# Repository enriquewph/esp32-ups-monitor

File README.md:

# Migrated
Pleas check [https://github.com/enriquewph/esp-map](https://github.com/enriquewph/esp-map)

# ups-central-fw
Firmware para ESP32 en UPS Central

# Necessary secrets.h file:
Place it here **lib/secrets/secrets.h**
It should have the next format
```c
#ifndef SECRETS_H
#define SECRETS_H

#define WIFI_SSID "MyWiFiSSID"
#define WIFI_PW "some_secret_password"

#endif
```

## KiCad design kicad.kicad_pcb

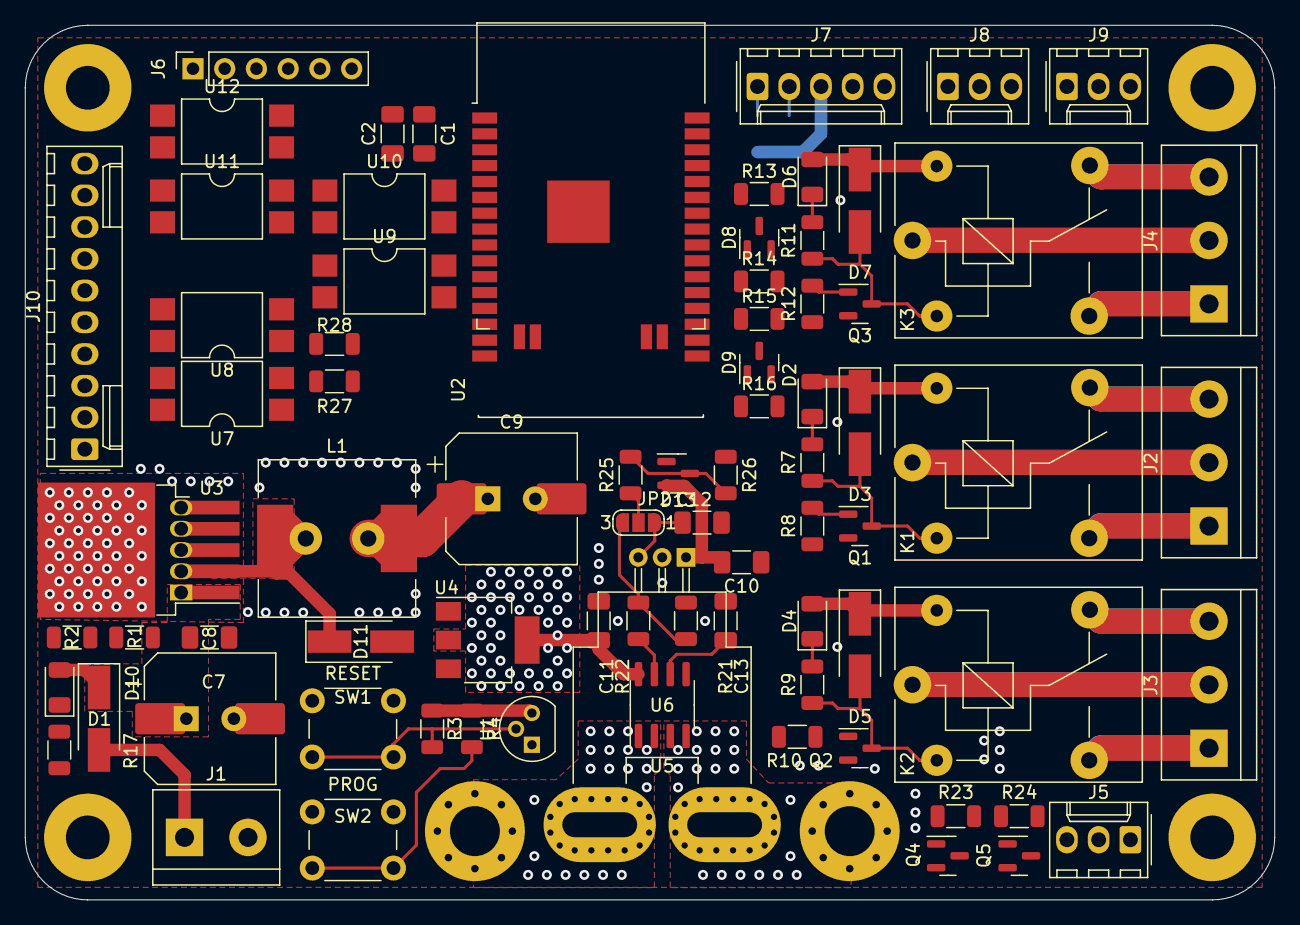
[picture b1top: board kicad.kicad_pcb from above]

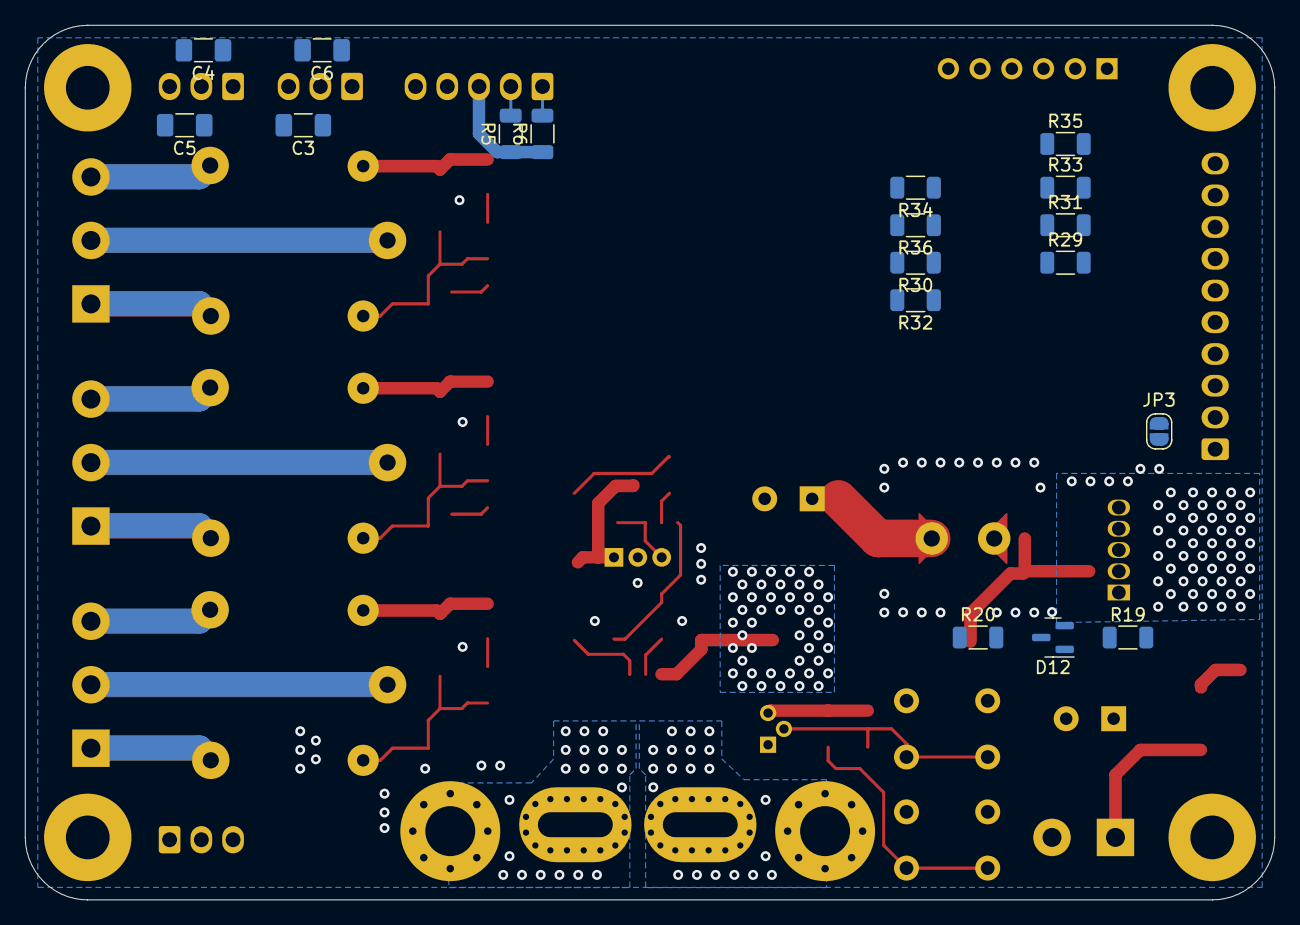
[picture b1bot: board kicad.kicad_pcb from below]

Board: 2 copper layers, 100.0 x 70.0 mm, 98 parts (18 on the bottom side), 77 nets.

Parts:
C1, C3, C4, C5, C6, C8, C10, C11, C12: 100nF; C_1206_3216Metric_Pad1.33x1.80mm_HandSolder
C2: 1uF; C_1206_3216Metric_Pad1.33x1.80mm_HandSolder
C7, C9: 470uF; CAP_10x10_SMD_THT
C13: 1nF; C_1206_3216Metric_Pad1.33x1.80mm_HandSolder
D1, D11: SS14; D_SMA_Handsoldering
D2, D4, D6, D10: LED; LED_1206_3216Metric
D3, D5, D7: M7; D_SMA_Handsoldering
D8, D9, D12, D13: BAT54S; SOT-23
H1, H2: MountingHole_Pad; MountingHole_4mm_Pad_Via
J1: Screw_Terminal_01x02; TerminalBlock_bornier-2_P5.08mm
J2, J3, J4: Screw_Terminal_01x03; TerminalBlock_bornier-3_P5.08mm
J5, J8, J9: Conn_01x03; Molex_KK-254_AE-6410-03A_1x03_P2.54mm_Vertical
J6: ICSP; PinSocket_1x06_P2.54mm_Vertical
J7: Conn_01x05; Molex_KK-254_AE-6410-05A_1x05_P2.54mm_Vertical
J10: Conn_01x10; Molex_KK-254_AE-6410-10A_1x10_P2.54mm_Vertical
JP2: SolderJumper_3_Bridged12; SolderJumper-3_P1.3mm_Open_RoundedPad1.0x1.5mm_NumberLabels
JP3: SolderJumper_2_Open; SolderJumper-2_P1.3mm_Open_RoundedPad1.0x1.5mm
K1, K2, K3: RELAY; Relay_SPDT_SANYOU_SRD_Series_Form_C
L1: 68uH; L_12x12mm_H8mm
Q1, Q2, Q3, Q4: BC817; SOT-23
Q5: IRLML2502; SOT-23
R1: 22k; R_1206_3216Metric
R2: 5k6; R_1206_3216Metric
R3, R4, R5, R6, R24, R30, R32, R34, R36: 10k; R_1206_3216Metric
R7, R8, R9, R10, R11, R12, R13, R14, R15, R16, R17, R19, R20, R22, R23, R25, R26, R29, R31, R33, R35: 1k; R_1206_3216Metric
R21: 2k; R_1206_3216Metric
R27, R28: 100; R_1206_3216Metric
SW1, SW2: SW_Push; SW_PUSH_6mm
U1: DS1233A-10; TO-92
U2: ESP32; ESP32-WROOM-WROVER-NC
U3: LM2596S-3.3; TO-263-5_TabPin3
U4: AMS1117-5.0; SOT-223-3_TabPin2
U5: ACS759; Allegro_CB_PFF
U6: ACS712; SOIC-8_3.9x4.9mm_P1.27mm
U7, U8, U9, U10, U11, U12: PC817XI; SMDIP-4_W9.53mm

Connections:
+3V3: C1.1, C2.1, C4.1, C6.1, C9.1, C10.1, D8.2, D9.2, D12.2, D13.2, J6.6, J7.3, J8.1, J9.1, L1.2, R3.1, R4.1, R5.1, R6.1, R30.1, R32.1, R34.1, R36.1, U1.3 (VDD), U2.2 (VDD), U3.4 (FB), U5.1 (VCC), U8.1
+5V: C11.1, J7.4, U4.2 (VO), U6.8 (VCC)
+12V: C7.1, C8.1, D1.1 (K), D2.2 (A), D3.1 (K), D4.2 (A), D5.1 (K), D6.2 (A), D7.1 (K), D10.2 (A), J5.1, JP3.2 (B), K1.5, K2.5, K3.5, R1.1, R24.1, U3.1 (VIN), U4.3 (VI)
+BATT: D1.2 (A), J1.1
/Current Sensor/IP+: H1.1, U5.4 (IP+), U6.1 (IP+), U6.2 (IP+)
/Current Sensor/IP-: H2.1, U5.5 (IP-), U6.3 (IP-), U6.4 (IP-)
/Current Sensor/OUT: JP2.2 (C), R25.2
/Input Protection/IN: R1.2, R2.1, R19.2
/LM35: T1/OUT: C3.1, J8.2, R13.2
/LM35: T2/OUT: C5.1, J9.2, R15.2
/Opto I/O/input-0/A: J10.2, JP3.1 (A), R29.2, R31.2, R33.2, R35.2
/Opto I/O/input-0/K: J10.7, U9.2
/Opto I/O/input-1/K: J10.8, U10.2
/Opto I/O/input-2/K: J10.9, U11.2
/Opto I/O/input-3/K: J10.10, U12.2
/Opto I/O/output-0/C: J10.5, U8.4
/Opto I/O/output-0/E: J10.6, U8.3
/Opto I/O/output-1/C: J10.3, U7.4
/Opto I/O/output-1/E: J10.4, U7.3
/Relay 1/COM: J2.2, K1.1
/Relay 1/NC: J2.3, K1.4
/Relay 1/NO: J2.1, K1.3
/Relay 2/COM: J3.2, K2.1
/Relay 2/NC: J3.3, K2.4
/Relay 2/NO: J3.1, K2.3
/Relay 3/COM: J4.2, K3.1
/Relay 3/NC: J4.3, K3.4
/Relay 3/NO: J4.1, K3.3
/Salida MOSFET/OUT: J5.3, Q5.3 (D)
FAN_1: R23.2, U2.26 (IO4)
GND: C1.2, C2.2, C3.2, C4.2, C5.2, C6.2, C7.2, C8.2, C9.2, C10.2, C11.2, C12.2, C13.2, D8.1, D9.1, D11.2 (A), D12.1, D13.1, J1.2, J6.5, J7.5, J8.3, J9.3, J10.1, Q1.2 (E), Q2.2 (E), Q3.2 (E), Q4.2 (E), Q5.2 (S), R2.2, R17.2, R21.1, SW1.1, SW2.1, U1.1 (GND), U2.1 (GND), U2.15 (GND), U2.38 (GND), U2.39 (GND), U3.3 (GND), U3.5 (~ON/OFF), U4.1 (GND), U5.2 (GND), U6.5 (GND), U7.2, U9.3, U10.3, U11.3, U12.3
GPIO0: J6.4, R4.2, SW2.2, U2.25 (IO0)
IBAT: R26.1, U2.6 (IO34)
IN0: R30.2, U2.10 (IO25), U9.4
IN1: R32.2, U2.11 (IO26), U10.4
IN2: R34.2, U2.8 (IO32), U11.4
IN3: R36.2, U2.9 (IO33), U12.4
unnamed: C12.1, JP2.1 (A), U5.3 (VIOUT)
unnamed: C13.1, U6.6 (FILTER)
unnamed: D2.1 (K), R7.1
unnamed: D3.2 (A), K1.2, Q1.3 (C), R7.2
unnamed: D4.1 (K), R9.1
unnamed: D5.2 (A), K2.2, Q2.3 (C), R9.2
unnamed: D6.1 (K), R11.1
unnamed: D7.2 (A), K3.2, Q3.3 (C), R11.2
unnamed: D8.3, R13.1, R14.2
unnamed: D9.3, R15.1, R16.2
unnamed: D10.1 (K), R17.1
unnamed: D11.1 (K), L1.1, U3.2 (OUT)
unnamed: D12.3, R19.1, R20.2
unnamed: D13.3, R25.1, R26.2
unnamed: JP2.3 (B), R21.2, R22.1
unnamed: Q1.1 (B), R8.1
unnamed: Q2.1 (B), R10.1
unnamed: Q3.1 (B), R12.1
unnamed: Q4.1 (B), R23.1
unnamed: Q4.3 (C), Q5.1 (G), R24.2
unnamed: R22.2, U6.7 (VIOUT)
unnamed: R27.1, U7.1
unnamed: R28.1, U8.2
unnamed: R29.1, U9.1
unnamed: R31.1, U10.1
unnamed: R33.1, U11.1
unnamed: R35.1, U12.1
OUT0: R28.2, U2.30 (IO18)
OUT1: R27.2, U2.31 (IO19)
RELAY_1: R8.2, U2.16 (IO13)
RELAY_2: R10.2, U2.12 (IO27)
RELAY_3: R12.2, U2.37 (IO23)
RESET: J6.1, R3.2, SW1.2, U1.2 (~RESET), U2.3 (EN)
RXD0: J6.3, U2.34 (RXD0/IO3)
SCL: J7.1, R6.2, U2.36 (IO22)
SDA: J7.2, R5.2, U2.33 (IO21)
TBAT: R14.1, U2.5 (SENSOR_VN)
TEMP2: R16.1, U2.7 (IO35)
TXD0: J6.2, U2.35 (TXD0/IO1)
VBAT: R20.1, U2.4 (SENSOR_VP)

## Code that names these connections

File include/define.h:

#ifndef DEFINE_Y
#define DEFINE_Y

// GPIO DEFINITIONS

//bare int
#define PIN_VBAT            36
#define PIN_TBAT            39
#define PIN_IBAT            34
#define PIN_UPS_OFF          32
#define PIN_UPS_NORMAL      33
#define PIN_UPS_CARGA       25
#define PIN_UPS_INVERTER    26
#define PIN_RELAY_1         13
#define PIN_RELAY_2         27
#define PIN_FAN             4

//gpio_num_t
#define PIN_VBAT_GPIONUM            GPIO_NUM_36
#define PIN_TBAT_GPIONUM            GPIO_NUM_39
#define PIN_IBAT_GPIONUM            GPIO_NUM_34
#define PIN_UPS_OFF_GPIONUM          GPIO_NUM_32
#define PIN_UPS_NORMAL_GPIONUM      GPIO_NUM_33
#define PIN_UPS_CARGA_GPIONUM       GPIO_NUM_25
#define PIN_UPS_INVERTER_GPIONUM    GPIO_NUM_26
#define PIN_RELAY_1_GPIONUM         GPIO_NUM_13
#define PIN_RELAY_2_GPIONUM         GPIO_NUM_27
#define PIN_FAN_GPIONUM             GPIO_NUM_4

//adc1_channel_t
#define PIN_VBAT_ADC_CH ADC1_CHANNEL_0 //GPIO36 - ADC1_CH0 - RTCIO_0
#define PIN_TBAT_ADC_CH ADC1_CHANNEL_3 //GPIO39 - ADC1_CH3 - RTCIO_3
#define PIN_IBAT_ADC_CH ADC1_CHANNEL_6 //GPIO34 - ADC1_CH6 - RTCIO_4

#endif

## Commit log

2021-05-18 add license
2021-05-18 added secrets and platform changes.
2021-05-19 change to esp-idf(4.0.1) + arduino
2021-05-19 small changes
2021-05-19 moved some things over...
2021-05-25 add debug routines
2021-05-25 Add TCP socket debug support.
2021-05-25 add relay ctrl
2021-05-25 manejo basico de ups con debug.
2021-05-25 fue invertido el UPS_ON
2021-05-25 todo comment
2021-05-29 Añadir maquina de estados preliminar: #7
2021-05-29 add doxygen support
2021-05-29 Eliminado estado APAGADO. Comentarios varios #7
2021-05-29 changed include for future references. #7
2021-05-30 added several hal files, some work on cooling
2021-05-30 small change to doxygen config.
2021-05-30 changes to hal structure
2021-05-30 adjusted ADC.
2021-05-31 algunos cambios en la capa hal
2021-05-31 aumento del numero de muestras del adc
2021-05-31 aumentar variable de promedio p' prevenir overflow
2021-05-31 cambio al offset para correccion
2021-05-31 comentar codigo
2021-05-31 add relay to HAL
2021-05-31 add vbat hal files + renamy symbol
2021-06-02 add ups to hal
2021-06-02 add current to hal
2021-06-05 add state change functions.
2021-06-06 update debugcmd
2021-06-06 add ext lib
2021-06-06 add tcp status print.
2021-06-06 fix debug typo
2021-06-07 add kicad files
2021-06-07 add doxygen output
2021-06-08 Several changes.
2021-06-10 Full update to psu.sch
2021-06-10 updated all components
2021-06-10 various updates
2021-06-10 change layout
2021-06-26 Solves #26
2021-06-26 new footprints
2021-06-26 More footprints
2021-06-27 more footprints & 3d models
2021-06-27 Closes #17
2021-06-27 Closes #13
2021-06-27 Closes #14
2021-06-27 Closes #18
2021-06-27 Several changes
    Usando stock de http://tienda.ityt.com.ar/
2021-06-28 Closes #29
2022-06-26 routeo fase 1
2022-06-26 fix bugardo
2022-06-26 fix bugardo - update design rules
2022-06-27 fix bugardo - routeos principales
